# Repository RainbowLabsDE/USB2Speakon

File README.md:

# USB2Speakon

A fully self contained, USB powered ~5W PMPO[^1] Class-D amplifier inside a Speakon connector.  
This adapter allows you to connect your phone / laptop / $USB-audio-host-capable device to any passive loudspeaker that accepts a Speakon plug.  
In my tests it reached volumes significantly above "room volume". Its output power is probably enough to host a small indoor party.

<p float="left" style="display: flex; flex-wrap: wrap; align-items: center;">
  &nbsp;
  &nbsp;
  &nbsp;
  &nbsp;

</p>

### 3D-Printed Insert
The mechanical dimensions of the PCB and the insert were designed for a (now discontinued) [Neutrik speakON NL4FX](https://www.neutrik.com/en/product/nl4fx). 

The .step file can be found in the root of the repo and [the full design is on OnShape](https://cad.onshape.com/documents/68748694b7ef2772d9eb6de5/w/d122b393e16d1d6e538e0f7c/e/8ff2a0b1ab0e743580e4e000).

## Known "issues"
(Not really issues, as this project is more of an irl shitpost, so any issues are more or less by design :D)
- Android phones produce less volume than PCs. Idk why exactly, but it appears to be a software limitation, it's not limited by USB power. 
  - On some Android phones it's way too quiet though, there you can use [this shady volume booster app](https://play.google.com/store/apps/details?id=com.goodev.volume.booster) that actually manages to increase the output volume in that case.
- The project was designed for the now discontinued NL4FX. It is unclear if it would mechanically fit inside the new NL4FXX.
- ~~v0.1 has a 3225 footprint for a 6MHz crystal. No 6MHz crystal is available for that footprint tho.~~
  - This has been fixed in v0.2 with an oscillator.

## Pictures in use

[^1]: ~~Peak Music Power Output~~ Panel Melting Power Once

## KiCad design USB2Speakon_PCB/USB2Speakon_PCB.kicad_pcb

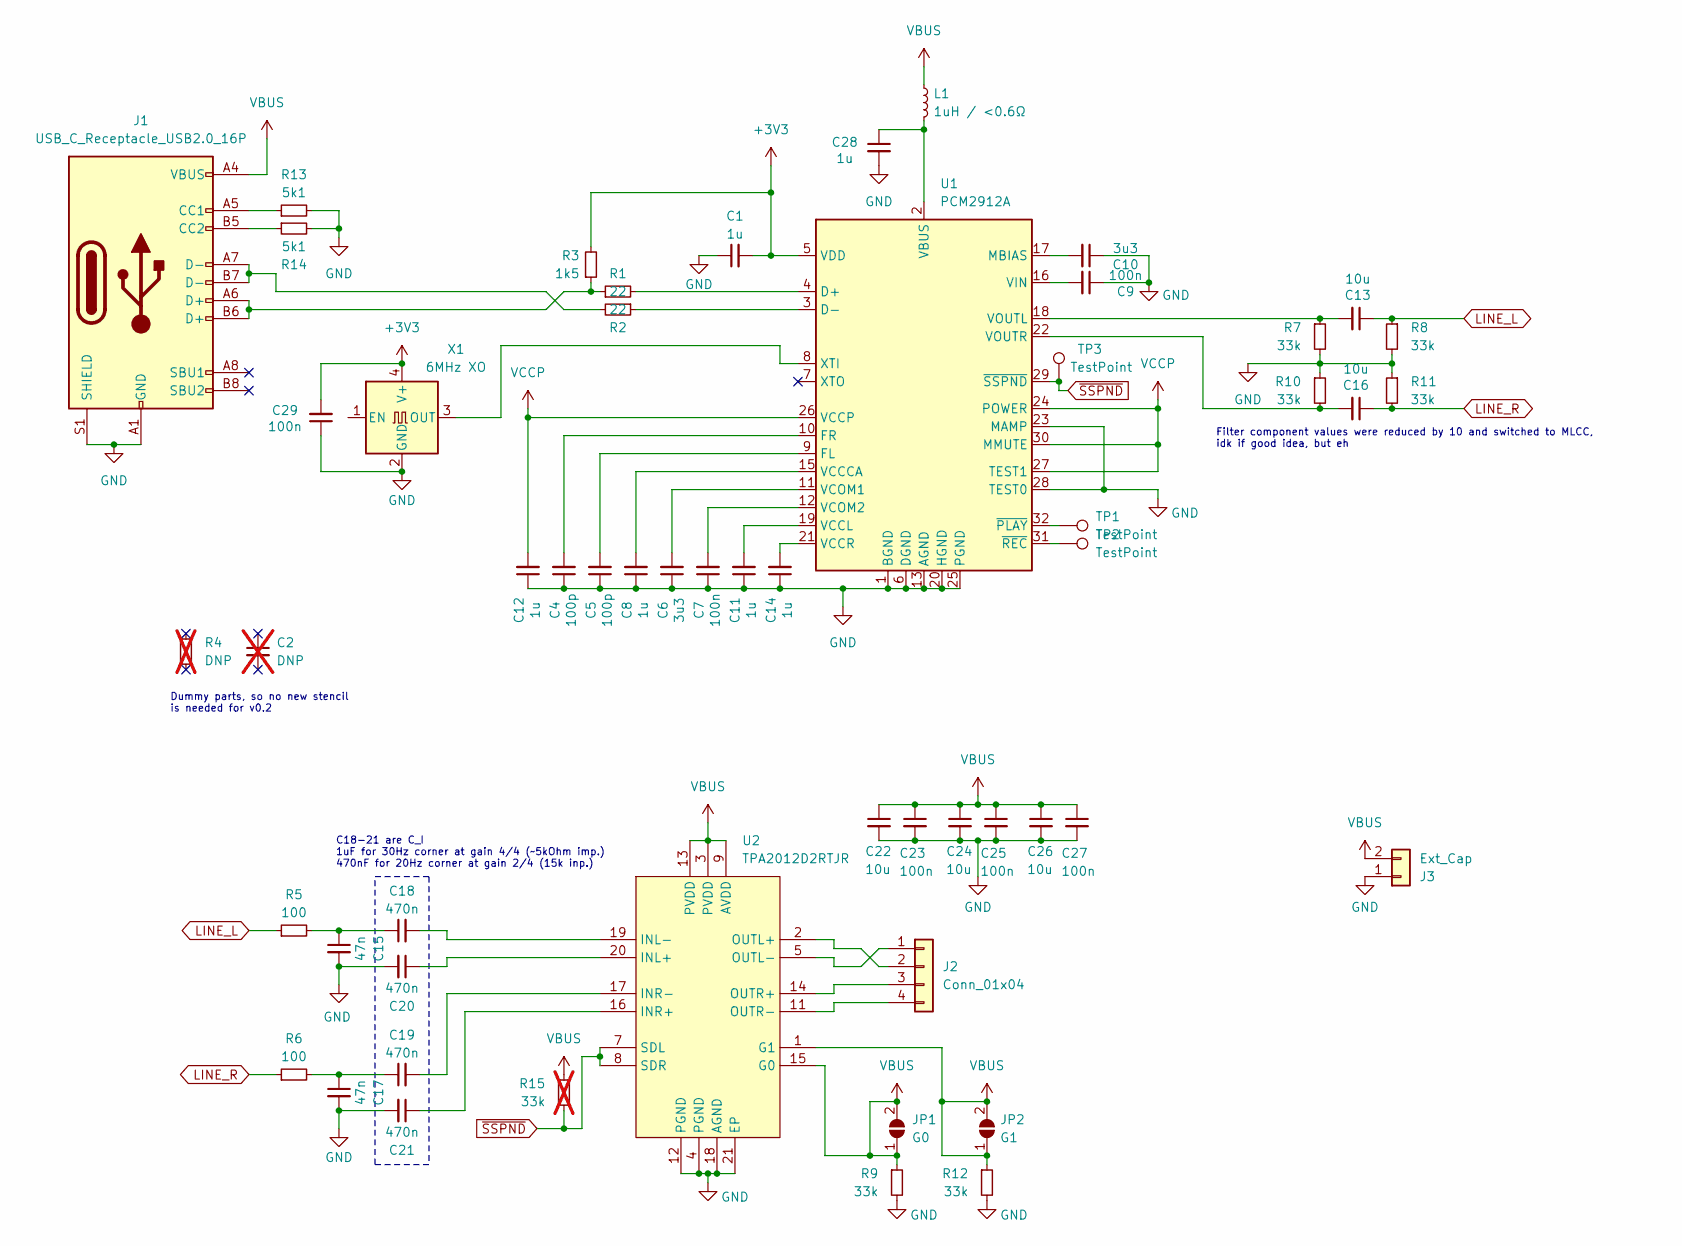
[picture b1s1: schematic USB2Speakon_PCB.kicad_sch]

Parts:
C1, C8, C11, C12, C14, C28: 1u; C_0402_1005Metric
C2: DNP; C_0402_1005Metric; not fitted
C4, C5: 100p; C_0402_1005Metric
C6, C10: 3u3; C_0402_1005Metric
C7, C9, C23, C25, C27, C29: 100n; C_0402_1005Metric
C13, C16, C22, C24, C26: 10u; C_0402_1005Metric
C15, C17: 47n; C_0402_1005Metric
C18, C19, C20, C21: 470n; C_0402_1005Metric
J1: USB_C_Receptacle_USB2.0_16P; USB_C_Receptacle_HRO_TYPE-C-31-M-12
J2: Conn_01x04; PinHeader_1x04_P2.54mm_Vertical
J3: Ext_Cap; PinSocket_1x02_P2.54mm_Vertical
JP1: G0; SolderJumper-2_P1.3mm_Open_TrianglePad1.0x1.5mm
JP2: G1; SolderJumper-2_P1.3mm_Open_TrianglePad1.0x1.5mm
L1: 1uH / <0.6Ω; L_0805_2012Metric; LCSC C99367
R1, R2: 22; R_0402_1005Metric
R3: 1k5; R_0402_1005Metric
R4: DNP; R_0402_1005Metric; not fitted
R5, R6: 100; R_0402_1005Metric
R7, R8, R9, R10, R11, R12: 33k; R_0402_1005Metric
R13, R14: 5k1; R_0402_1005Metric
R15: 33k; R_0402_1005Metric; not fitted
TP1, TP2, TP3: TestPoint; TestPoint_Pad_D1.0mm
U1: PCM2912A; TQFP-32_7x7mm_P0.8mm
U2: TPA2012D2RTJR; QFN-20-1EP_4x4mm_P0.5mm_EP2.7x2.7mm; LCSC Part C7717
X1: 6MHz XO; OSC-SMD_4P-L3.2-W2.5-BL

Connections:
+3V3: C1.2, C29.2, R3.2, U1.5 (VDD), X1.4 (V+)
GND: C1.1, C4.1, C5.1, C6.1, C7.1, C8.1, C9.1, C10.1, C11.1, C12.1, C14.1, C15.2, C17.2, C20.2, C21.2, C22.2, C23.2, C24.2, C25.2, C26.2, C27.2, C28.2, C29.1, J1.A1 (GND), J1.A12 (GND), J1.B1 (GND), J1.B12 (GND), J1.S1 (SHIELD), J3.1, R7.2, R8.2, R9.2, R10.1, R11.1, R12.2, R13.2, R14.2, U1.1 (BGND), U1.6 (DGND), U1.13 (AGND), U1.20 (HGND), U1.23 (MAMP), U1.25 (PGND), U1.28 (TEST0), U2.4 (PGND), U2.12 (PGND), U2.18 (AGND), U2.21 (EP), X1.2 (GND)
LINE_L: C13.1, R5.1, R8.1
LINE_R: C16.1, R6.1, R11.2
unnamed: C15.1, C18.1, R5.2
unnamed: C17.1, C19.1, R6.2
unnamed: J1.A5 (CC1), R13.1
unnamed: J1.B5 (CC2), R14.1
unnamed: J1.A6 (D+), J1.B6 (D+), R1.1, R3.1
unnamed: J1.A7 (D-), J1.B7 (D-), R2.2
unnamed: J2.1, U2.5 (OUTL-)
unnamed: J2.2, U2.2 (OUTL+)
unnamed: J2.3, U2.14 (OUTR+)
unnamed: J2.4, U2.11 (OUTR-)
unnamed: R1.2, U1.4 (D+)
unnamed: R2.1, U1.3 (D-)
unnamed: C5.2, U1.9 (FL)
unnamed: C4.2, U1.10 (FR)
unnamed: C10.2, U1.17 (MBIAS)
unnamed: C28.1, L1.2, U1.2 (VBUS)
unnamed: C8.2, U1.15 (VCCCA)
unnamed: C11.2, U1.19 (VCCL)
unnamed: C14.2, U1.21 (VCCR)
unnamed: C6.2, U1.11 (VCOM1)
unnamed: C7.2, U1.12 (VCOM2)
unnamed: C9.2, U1.16 (VIN)
unnamed: C13.2, R7.1, U1.18 (VOUTL)
unnamed: C16.2, R10.2, U1.22 (VOUTR)
unnamed: U1.8 (XTI), X1.3 (OUT)
unnamed: TP1.1, U1.32 (~PLAY)
unnamed: TP2.1, U1.31 (~REC)
unnamed: C20.1, U2.20 (INL+)
unnamed: C18.2, U2.19 (INL-)
unnamed: C21.1, U2.16 (INR+)
unnamed: C19.2, U2.17 (INR-)
VBUS: C22.1, C23.1, C24.1, C25.1, C26.1, C27.1, J1.A4 (VBUS), J1.A9 (VBUS), J1.B4 (VBUS), J1.B9 (VBUS), J3.2, JP1.1 (A), JP1.2 (B), JP2.1 (A), JP2.2 (B), L1.1, R9.1, R12.1, R15.1, U2.1 (G1), U2.3 (PVDD), U2.9 (AVDD), U2.13 (PVDD), U2.15 (G0)
VCCP: C12.2, U1.24 (POWER), U1.26 (VCCP), U1.27 (TEST1), U1.30 (MMUTE)
~SSPND: R15.2, TP3.1, U1.29 (~SSPND), U2.7 (SDL), U2.8 (SDR)

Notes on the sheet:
C18-21 are C_I 1uF for 30Hz corner at gain 4/4 (~5kOhm imp.) 470nF for 20Hz corner at gain 2/4 (15k inp.)
Filter component values were reduced by 10 and switched to MLCC, idk if good idea, but eh
Dummy parts, so no new stencil is needed for v0.2

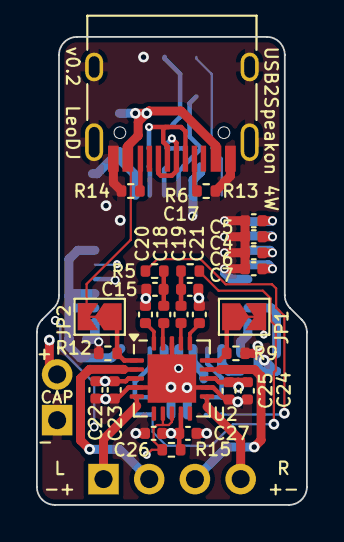
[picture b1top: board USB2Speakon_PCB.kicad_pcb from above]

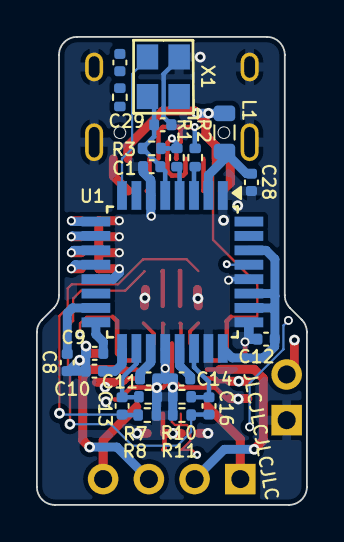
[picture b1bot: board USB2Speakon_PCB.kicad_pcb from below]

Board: 4 copper layers, 15.0 x 26.0 mm, 52 parts (23 on the bottom side), 36 nets.

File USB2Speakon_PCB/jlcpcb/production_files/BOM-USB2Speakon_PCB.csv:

Comment,Designator,Footprint,LCSC
USB_C_Receptacle_USB2.0_16P,J1,USB_C_Receptacle_HRO_TYPE-C-31-M-12,C165948
6MHz XO,X1,OSC-SMD_4P-L3.2-W2.5-BL,C2901554
PCM2912A,U1,TQFP-32_7x7mm_P0.8mm,C475497
3u3,"C10,C6",C_0402_1005Metric,C695126
TPA2012D2RTJR,U2,QFN-20-1EP_4x4mm_P0.5mm_EP2.7x2.7mm,C7717
1uH / <0.6Ω,L1,L_0805_2012Metric,C99367
1u,C28,C_0402_1005Metric,
33k,R9,R_0402_1005Metric,
100p,C5,C_0402_1005Metric,
47n,C17,C_0402_1005Metric,
10u,C22,C_0402_1005Metric,
10u,C24,C_0402_1005Metric,
470n,C20,C_0402_1005Metric,
470n,C18,C_0402_1005Metric,
470n,C21,C_0402_1005Metric,
47n,C15,C_0402_1005Metric,
100p,C4,C_0402_1005Metric,
5k1,R13,R_0402_1005Metric,
5k1,R14,R_0402_1005Metric,
100n,C25,C_0402_1005Metric,
100,R6,R_0402_1005Metric,
100n,C27,C_0402_1005Metric,
10u,C26,C_0402_1005Metric,
G0,JP1,SolderJumper-2_P1.3mm_Open_TrianglePad1.0x1.5mm,
470n,C19,C_0402_1005Metric,
100,R5,R_0402_1005Metric,
100n,C23,C_0402_1005Metric,
G1,JP2,SolderJumper-2_P1.3mm_Open_TrianglePad1.0x1.5mm,
33k,R12,R_0402_1005Metric,
100n,C7,C_0402_1005Metric,
33k,R7,R_0402_1005Metric,
33k,R10,R_0402_1005Metric,
22,R2,R_0402_1005Metric,
1u,C8,C_0402_1005Metric,
33k,R11,R_0402_1005Metric,
100n,C9,C_0402_1005Metric,
33k,R15,R_0402_1005Metric,
33k,R8,R_0402_1005Metric,
10u,C16,C_0402_1005Metric,
22,R1,R_0402_1005Metric,
1k5,R3,R_0402_1005Metric,
1u,C14,C_0402_1005Metric,
1u,C12,C_0402_1005Metric,
10u,C13,C_0402_1005Metric,
1u,C1,C_0402_1005Metric,
1u,C11,C_0402_1005Metric,
100n,C29,C_0402_1005Metric,

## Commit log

2024-03-12 rough layout of v0.1 done
2024-03-12 add production files (and some minor tweaks)
2024-05-10 some minor changes, idk
2024-05-10 add readme + license
2024-05-10 add in use image
2024-05-13 replace crystal with oscillator and add solder pads for a capacitor
